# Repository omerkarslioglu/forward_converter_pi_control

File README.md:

# Forwar Converter With PI Controller
9-36V Input Voltage, 28 Output Voltage, All Ripple: %2, 50KHz, 50 Watt DC-DC Forward Converter Design And Production

The aim of the project is to design and produce a dc-dc forward converter according to following
requirements:
Vin: 36-9 V,
Vout: 28 V,
Power: 50 Watt,
Ripple Ratings: 2%,
Fsw : 50 KHz,
Control System: PI with a STM32F4 MCU.
In addition to this, this paper shows formulas, calculations, experimental and simulation results of dc-dc
forward converter.

# Forward Converter
A forward converter is a switched-mode power supply (SMPS) circuit that transfers energy to
secondary side from primary side and ensures to decrease secondary side input voltage. Forward
converter circuit is similar to the fly-back converter circuit but it is more efficient than fly-back
converter circuit. Forward converter is mainly used for the application which requires higher power
output.
Secondary side of forward converter basicly derives from buck converter. But forward converter can
increase or decrease the input voltage thanks to transformer.
Forward converter is an isolated circuit as it has transformer.

As per the above block diagram, when the switch is turned ON, the input is applied to the primary
winding of the transformer and a voltage is appeared at the secondary winding of transformer.
Therefore, the dot polarity of the windings of transformer is positive, due to this the diode D1 gets
forward biased. Then the output voltage of the transformer is fed to the low pass filter circuit which is
connected to the load. When switch is turned OFF, the current in the windings of transformer comes
down to zero (assuming the transformer to be ideal).
A typical forward converter consists of a:
 Transformer which is either a step-up or step-down with a single or multiple secondary
windings. The type used depends on the available input voltage and desired output voltage. It
also provides isolation of the load from the input voltage.
- Switching components
- Diodes
- Capacitors
- Inductor

# Circuit Design For Simulation On Simulink

The all calculations, values and simulations result in the report.

# Circuit Schematic

# PCB Design

# About Software
As it is known, this designed circuit is designed as a close loop system and will be controlled by
PI. The software of this circuit works as follows: voltage is read with ADC and required ratio
calculation is made. This calculated value enters the PI algorithm and is compared with the
setpoint. If this value is not the same as the setpoint, the PI calculates a new value close to or the
same as the setpoint. This value is again proportioned and the PWM signal driving the mosfet is
updated again.

The closed loop system of Forward Converter is as above diagram. It is PID system. But Kd equals 0
as seting PI.
The software generally consists of two or three main modules:
1. main.c : It is the file where all the configurations are found, the main algorithm and PWM are
set.
2. ADC_READ.c : It is an analog reading value module that I developed specially for the
STM32F4 discovery board.
3. PID.c : It is the module where I wrote the PID algorithm.
Other folders belong to the HAL Library used and the processor's drivers.

All necessary explanations are in the software modules in the software folder in the project file.

Product:

If you have any question, you can contact me.

Omer Karslioglu
omerkarsliogluu@gmail.com

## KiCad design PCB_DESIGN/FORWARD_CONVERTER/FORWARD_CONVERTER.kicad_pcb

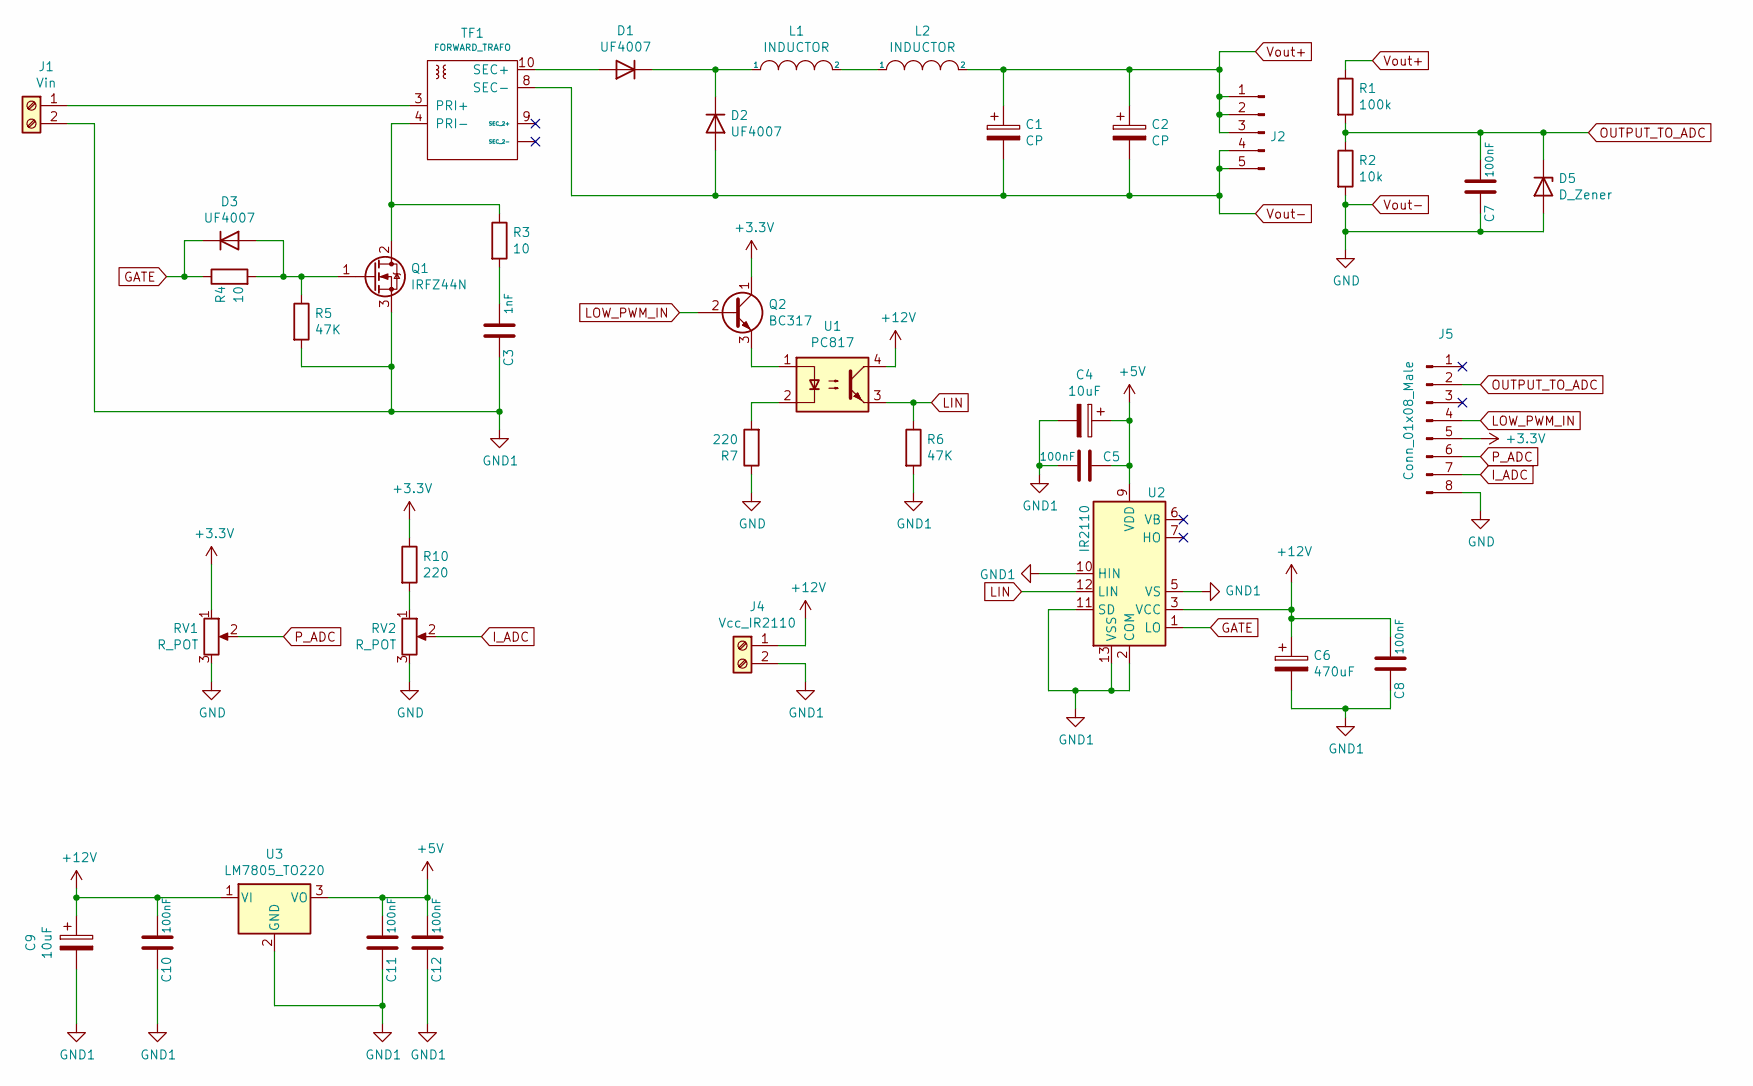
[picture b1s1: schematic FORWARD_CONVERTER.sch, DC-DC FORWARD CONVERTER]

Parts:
C1, C2: CP; CP_Radial_D12.5mm_P7.50mm
C3: 1nF; CP_Radial_D5.0mm_P2.50mm
C4, C9: 10uF; CP_Radial_D12.5mm_P5.00mm
C5, C7, C8, C10, C11, C12: 100nF; CP_Radial_D5.0mm_P2.50mm
C6: 470uF; CP_Radial_D12.5mm_P7.50mm
D1, D2, D3: UF4007; D_DO-41_SOD81_P12.70mm_Horizontal
D5: D_Zener; D_5W_P12.70mm_Horizontal
J1: Vin; TerminalBlock_bornier-2_P5.08mm
J2: Conn_01x05_Male; PinHeader_1x05_P2.54mm_Vertical
J4: Vcc_IR2110; TerminalBlock_bornier-2_P5.08mm
J5: Conn_01x08_Male; PinHeader_1x08_P2.54mm_Vertical
L1: INDUCTOR; L_Axial_L26.7mm_D14.0mm_P7.62mm_Vertical_Vishay_IHA-104
L2: INDUCTOR; L_Axial_L26.0mm_D11.0mm_P5.08mm_Vertical_Fastron_77A
Q1: IRFZ44N; TO-220-3_Vertical
Q2: BC317; TO-92_Inline
R1: 100k; R_Axial_DIN0411_L9.9mm_D3.6mm_P12.70mm_Horizontal
R2: 10k; R_Axial_DIN0411_L9.9mm_D3.6mm_P12.70mm_Horizontal
R3, R4: 10; R_Axial_DIN0411_L9.9mm_D3.6mm_P12.70mm_Horizontal
R5, R6: 47K; R_Axial_DIN0411_L9.9mm_D3.6mm_P12.70mm_Horizontal
R7, R10: 220; R_Axial_DIN0411_L9.9mm_D3.6mm_P12.70mm_Horizontal
RV1, RV2: R_POT; Potentiometer_Alps_RK163_Single_Horizontal
TF1: FORWARD_TRAFO
U1: PC817; DIP-4_W10.16mm
U2: IR2110; DIP-14_W7.62mm
U3: LM7805_TO220; TO-220-3_Vertical

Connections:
+3V3: J5.5, Q2.1 (C), R10.1, RV1.1
+5V: C4.1, C5.1, C11.2, C12.2, U2.9 (VDD), U3.3 (VO)
+12V: C6.1, C8.2, C9.1, C10.2, J4.1, U1.4, U2.3 (VCC), U3.1 (VI)
GATE: D3.1 (K), R4.1, U2.1 (LO)
GND1: C3.1, C4.2, C5.2, C6.2, C8.1, C9.2, C10.1, C11.1, C12.1, J1.2, J4.2, Q1.3 (S), R5.2, R6.2, U2.2 (COM), U2.5 (VS), U2.10 (HIN), U2.11 (SD), U2.13 (VSS), U3.2 (GND)
I_ADC: J5.7, RV2.2
LIN: R6.1, U1.3, U2.12 (LIN)
LOW_PWM_IN: J5.4, Q2.2 (B)
unnamed: C3.2, R3.2
unnamed: D1.1 (K), D2.1 (K), L1.1
unnamed: D1.2 (A), TF1.10 (SEC+)
unnamed: D3.2 (A), Q1.1 (G), R4.2, R5.1
unnamed: J1.1, TF1.3 (PRI+)
unnamed: L1.2, L2.1
unnamed: Q1.2 (D), R3.1, TF1.4 (PRI-)
unnamed: Q2.3 (E), U1.1
unnamed: R7.2, U1.2
unnamed: R10.2, RV2.1
OUTPUT_TO_ADC: C7.2, D5.1 (K), J5.2, R1.2, R2.1
P_ADC: J5.6, RV1.2
Vout+: C1.1, C2.1, J2.1, J2.2, J2.3, L2.2, R1.1
Vout-: C1.2, C2.2, C7.1, D2.2 (A), D5.2 (A), J2.4, J2.5, J5.8, R2.2, R7.1, RV1.3, RV2.3, TF1.8 (SEC-)

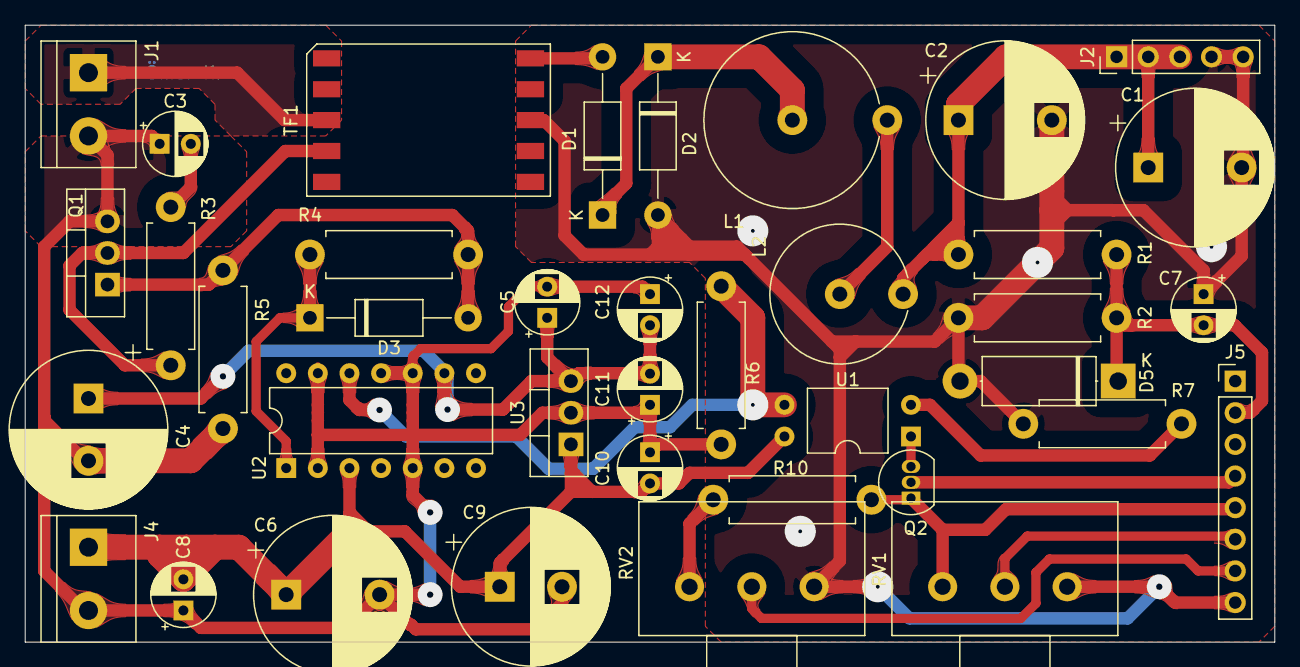
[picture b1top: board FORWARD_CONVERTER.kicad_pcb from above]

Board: 2 copper layers, 100.3 x 49.5 mm, 38 parts (0 on the bottom side), 22 nets.

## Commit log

2022-06-20 Create SOFTWARE
